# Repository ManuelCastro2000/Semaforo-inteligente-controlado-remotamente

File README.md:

# Semaforo-inteligente-controlado-remotamente

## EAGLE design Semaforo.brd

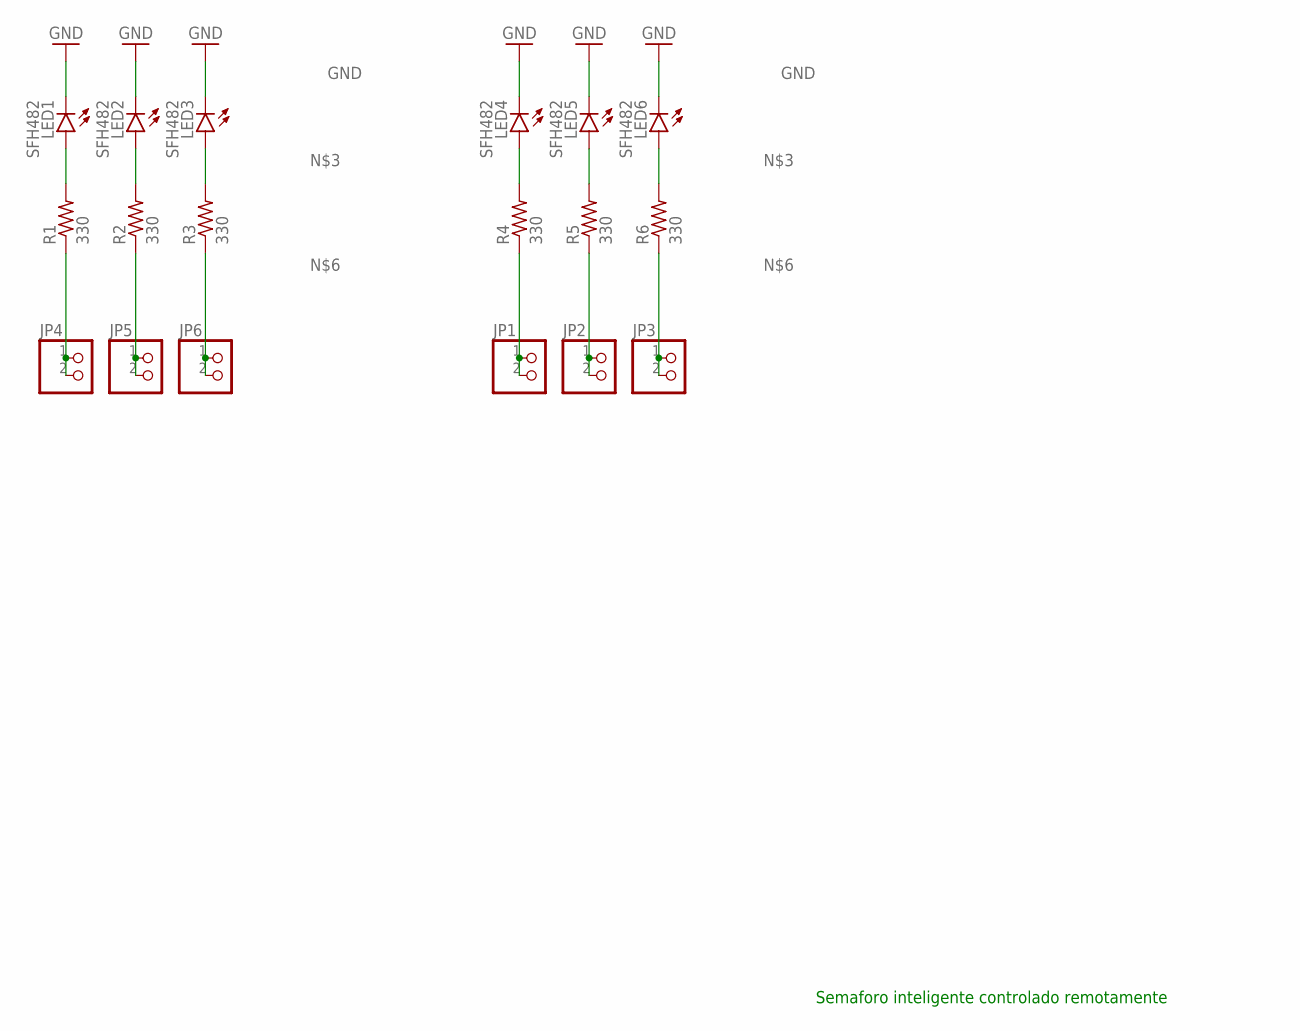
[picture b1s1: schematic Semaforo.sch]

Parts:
JP1, JP2, JP3, JP4, JP5, JP6: PINHD-1X2; 1X02
LED1, LED2, LED3, LED4, LED5, LED6: SFH482
R1, R2, R3, R4, R5, R6: 330; 0207/15

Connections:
GND: LED1.K (C), LED2.K (C), LED3.K (C), LED4.K (C), LED5.K (C), LED6.K (C)
unnamed: LED1.A, R1.2
unnamed: LED2.A, R2.2
unnamed: LED3.A, LED6.A, R3.2, R6.2
unnamed: JP4.1, JP4.2, R1.1
unnamed: JP5.1, JP5.2, R2.1
unnamed: JP3.1, JP3.2, JP6.1, JP6.2, R3.1, R6.1
unnamed: LED4.A, R4.2
unnamed: LED5.A, R5.2
unnamed: JP1.1, JP1.2, R4.1
unnamed: JP2.1, JP2.2, R5.1

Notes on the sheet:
Semaforo inteligente controlado remotamente

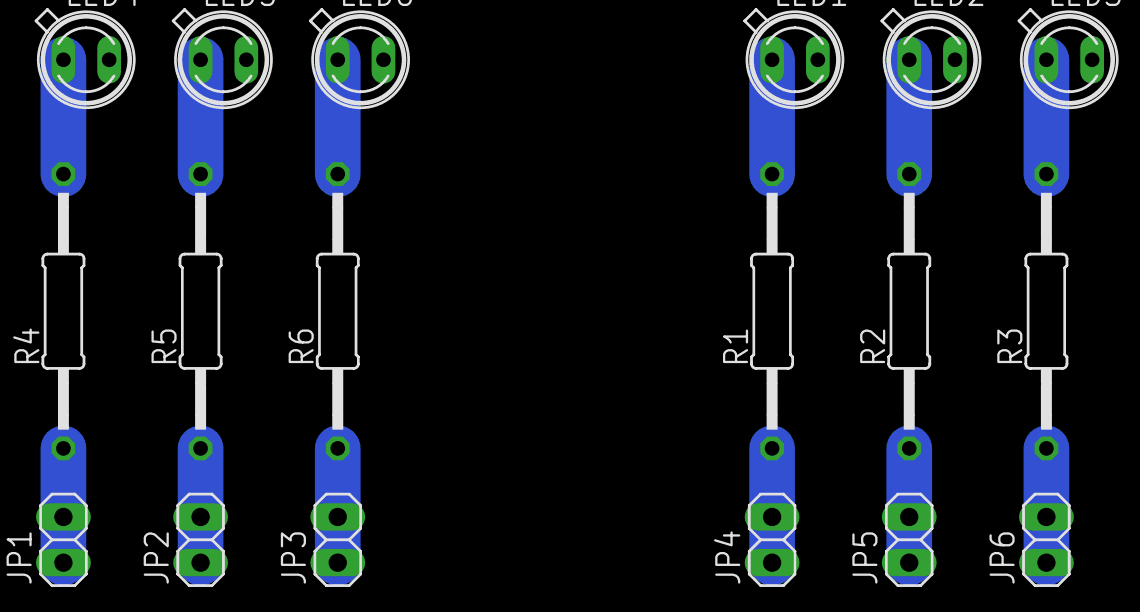
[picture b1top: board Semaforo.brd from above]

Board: 2 copper layers, 18 parts (0 on the bottom side), 11 nets.
